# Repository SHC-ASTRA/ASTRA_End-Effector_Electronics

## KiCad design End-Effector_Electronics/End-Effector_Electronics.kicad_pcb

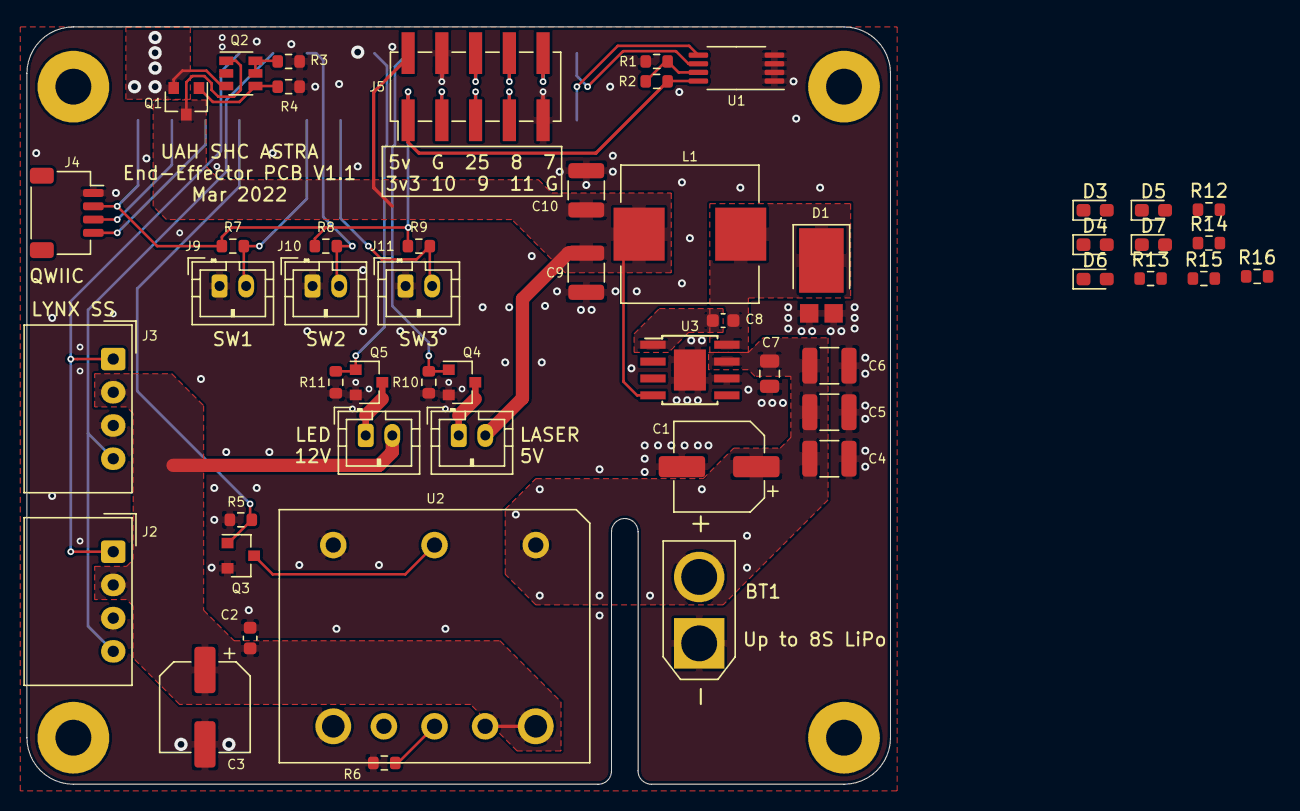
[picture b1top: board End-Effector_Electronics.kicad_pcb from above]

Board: 2 copper layers, 65.0 x 57.0 mm, 56 parts (1 on the bottom side), 38 nets.

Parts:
BT1: XT_Battery_Connector; AMASS_XT30U-M_1x02_P5.0mm_Vertical
C1: 33u; CP_Elec_6.3x5.4
C2: 0.1u; C_0603_1608Metric
C3: 22uF; CP_Elec_6.3x5.4
C4, C5, C6: 10u; C_1210_3225Metric
C7: 1u; C_0805_2012Metric
C8: 10n; C_0603_1608Metric
C9, C10: 47u; C_1210_3225Metric
D1: D_Schottky; D_PowerDI-5
D2: LED; JST_PH_B2B-PH-K_1x02_P2.00mm_Vertical
D3, D4, D5, D6, D7: G; LED_0603_1608Metric_Pad1.05x0.95mm_HandSolder
H1, H2, H3, H4: MountingHole_Pad; MountingHole_2.7mm_M2.5_Pad
J1: Raspberry_Pi_2_3; PinSocket_2x20_P2.54mm_Vertical_SMD
J2, J3: LynxServo; Molex_SPOX_5268-04A_1x04_P2.50mm_Horizontal
J4: QWIIC_Generic_Conn; JST_SH_SM04B-SRSS-TB_1x04-1MP_P1.00mm_Horizontal
J5: Conn_02x05_Odd_Even; PinHeader_2x05_P2.54mm_Vertical_SMD
J9, J10, J11: SW_Push_Open; JST_PH_B2B-PH-K_1x02_P2.00mm_Vertical
L1: 18u; L_Wuerth_HCI-1050
LD1: Laserdiode_1C2A; JST_PH_B2B-PH-K_1x02_P2.00mm_Vertical
Q1: Q_PMOS_GSD; SOT-23
Q2: DMMT3906; SOT-23-6
Q3, Q4, Q5: Q_NMOS_GSD; SOT-23
R1: DNP; R_0603_1608Metric
R2, R3: 10k; R_0603_1608Metric
R4: 47k; R_0603_1608Metric
R5, R7, R8, R9, R10, R11: 100k; R_0603_1608Metric
R6: 1.82k; R_0603_1608Metric
R12: 10; R_0603_1608Metric
R13, R14: 180; R_0603_1608Metric
R15: 1k; R_0603_1608Metric
R16: 3.3k; R_0603_1608Metric
U1: CAT24C32; TSSOP-8_4.4x3mm_P0.65mm
U2: TDK_I3A4W008A033V; Power_Supply_32nd_Brick
U3: LM22676MR-5; TI_SO-PowerPAD-8

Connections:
+3V3: D3.2, J1.1, J1.17, J4.2, J5.1, R2.2, R7.1, R8.1, R9.1, U1.8
+5V: C9.1, C10.1, D4.2, J5.2, L1.2, LD1.2, Q1.3, Q2.1, U3.4
+12V: C2.1, C3.1, D2.2, D6.2, J2.2, J3.2, U2.7, U2.8
+BATT: BT1.2, C1.1, C4.1, C5.1, C6.1, C7.1, D7.2, U2.1, U3.7
/5V_RPI: D5.2, J1.2, J1.4, Q1.2, Q2.3
/12V_Disable: J1.7, Q3.1, R5.1
/GPIO7: J1.26, J5.10
/GPIO8: J1.24, J5.8
/GPIO9: J1.21, J5.5
/GPIO10: J1.19, J5.3
/GPIO11: J1.23, J5.7
/GPIO25: J1.22, J5.6
/ID_SCL: J1.28, U1.6
/ID_SDA: J1.27, U1.5
/LED: J1.16, Q5.1, R11.1
/Laser: J1.18, Q4.1, R10.1
/Limit_SW1: J1.11, J9.2, R7.2
/Limit_SW2: J1.12, J10.2, R8.2
/Limit_SW3: J1.13, J11.2, R9.2
/SCL: J1.5, J4.4
/SDA: J1.3, J4.3
/ServoRX: J1.8, J2.1, J3.1
/ServoTX: J1.10, J2.4, J3.4
GND: BT1.1, C1.2, C2.2, C3.2, C4.2, C5.2, C6.2, C7.2, C9.2, C10.2, D1.2, J1.6, J1.9, J1.14, J1.20, J1.25, J1.30, J1.34, J1.39, J2.3, J3.3, J4.1, J5.4, J5.9, J9.1, J10.1, J11.1, Q3.2, Q4.2, Q5.2, R1.2, R3.1, R4.2, R5.2, R6.2, R10.2, R11.2, R12.2, R13.2, R14.2, R15.2, R16.2, U1.1, U1.2, U1.3, U1.4, U2.3, U2.4, U3.6, U3.9
unnamed: C8.1, U3.1
unnamed: C8.2, D1.1, L1.1, U3.8
unnamed: D2.1, Q5.3
unnamed: D3.1, R12.1
unnamed: D4.1, R13.1
unnamed: D5.1, R14.1
unnamed: D6.1, R15.1
unnamed: D7.1, R16.1
unnamed: LD1.1, Q4.3
unnamed: Q1.1, Q2.4, R4.1
unnamed: Q2.5, Q2.6, R3.2
unnamed: Q3.3, U2.2
unnamed: R1.1, R2.1, U1.7
unnamed: R6.1, U2.6

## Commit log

2021-10-23 Added KiCAD Files
2021-10-30 Forgot to check out
2021-10-30 Added a few components
2021-10-30 Added libraries
    libraries. Replaced BNO055
2021-10-30 added sheet for 5v supply
2021-10-30 5V supply added
2021-10-30 12v supply
    and bno
2021-10-30 Fixed broken thingy
2021-10-30 Added some stuff
    very description
2021-11-06 Forgot to commit latest changes
2021-11-13 Started associating components
2021-11-19 Worked on finding components
2021-11-19 More component part selection
2021-11-19 forgot to save
2021-11-20 finished associating part nums and footprints
2021-11-21 Finished layout and routing of initial components
2021-11-21 added things and cleaned up silkscreen
2021-11-21 Swapped a few components
2021-11-21 tweaks
2021-11-21 Fixed errors
2021-12-16 I changed something I guess?
2022-03-14 Started post SAR fixes
2022-03-15 indicator LEDs
2022-03-17 Indicator LEDs in PCB
2022-03-17 Update End-Effector_Electronics.sch-bak
